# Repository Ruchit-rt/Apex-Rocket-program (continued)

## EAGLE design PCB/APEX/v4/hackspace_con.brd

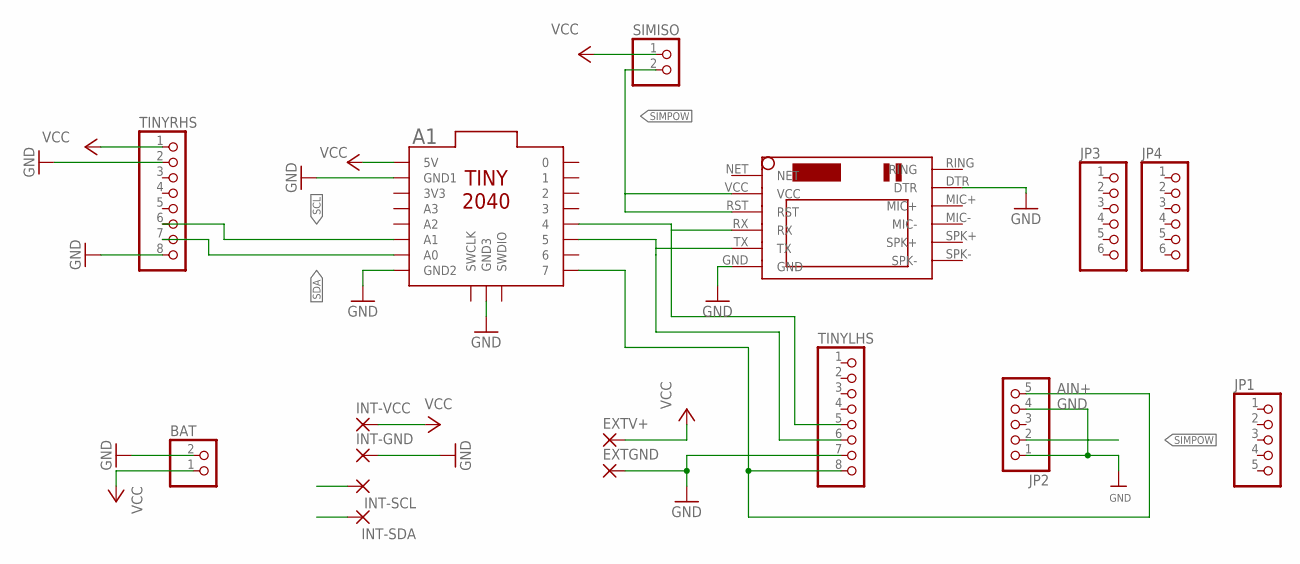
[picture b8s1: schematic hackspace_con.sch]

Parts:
A1: TINY2040
BAT: JST_2PIN-THM-RA; JST-PH-2-THM-RA
EXTGND: SMD5; SMD2,54-5,08
EXTV+: SMD5; SMD2,54-5,08
INT-GND: 3,17/1,1
INT-SCL: 3,17/1,1
INT-SDA: 3,17/1,1
INT-VCC: 3,17/1,1
JP1: PINHD-1X5; 1X05
JP2: HEADER-1X570MIL; 1X05_ROUND_70
JP3, JP4: PINHD-1X6; 1X06
SIMISO: PINHD-1X2; 1X02
TINYLHS: PINHD-1X8; 1X08
TINYRHS: PINHD-1X8; 1X08
U$1: SIM800LMODULE

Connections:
AIN+: A1.7, JP2.5, TINYLHS.8
GND: A1.GND1, A1.GND2, A1.GND3, BAT.2 (1), EXTGND.1, INT-GND.1, JP2.1, JP2.4, TINYLHS.7, TINYRHS.2, TINYRHS.8, U$1.DTR, U$1.GND
RX: A1.4, TINYLHS.5, U$1.RX
SCL: A1.A1, INT-SCL.1, TINYRHS.6
SDA: A1.A0, INT-SDA.1, TINYRHS.7
SIMPOW: JP2.2, SIMISO.2, U$1.RST, U$1.VCC
TX: A1.5, TINYLHS.6, U$1.TX
VCC: A1.5V, BAT.1 (2), EXTV+.1, INT-VCC.1, SIMISO.1, TINYRHS.1

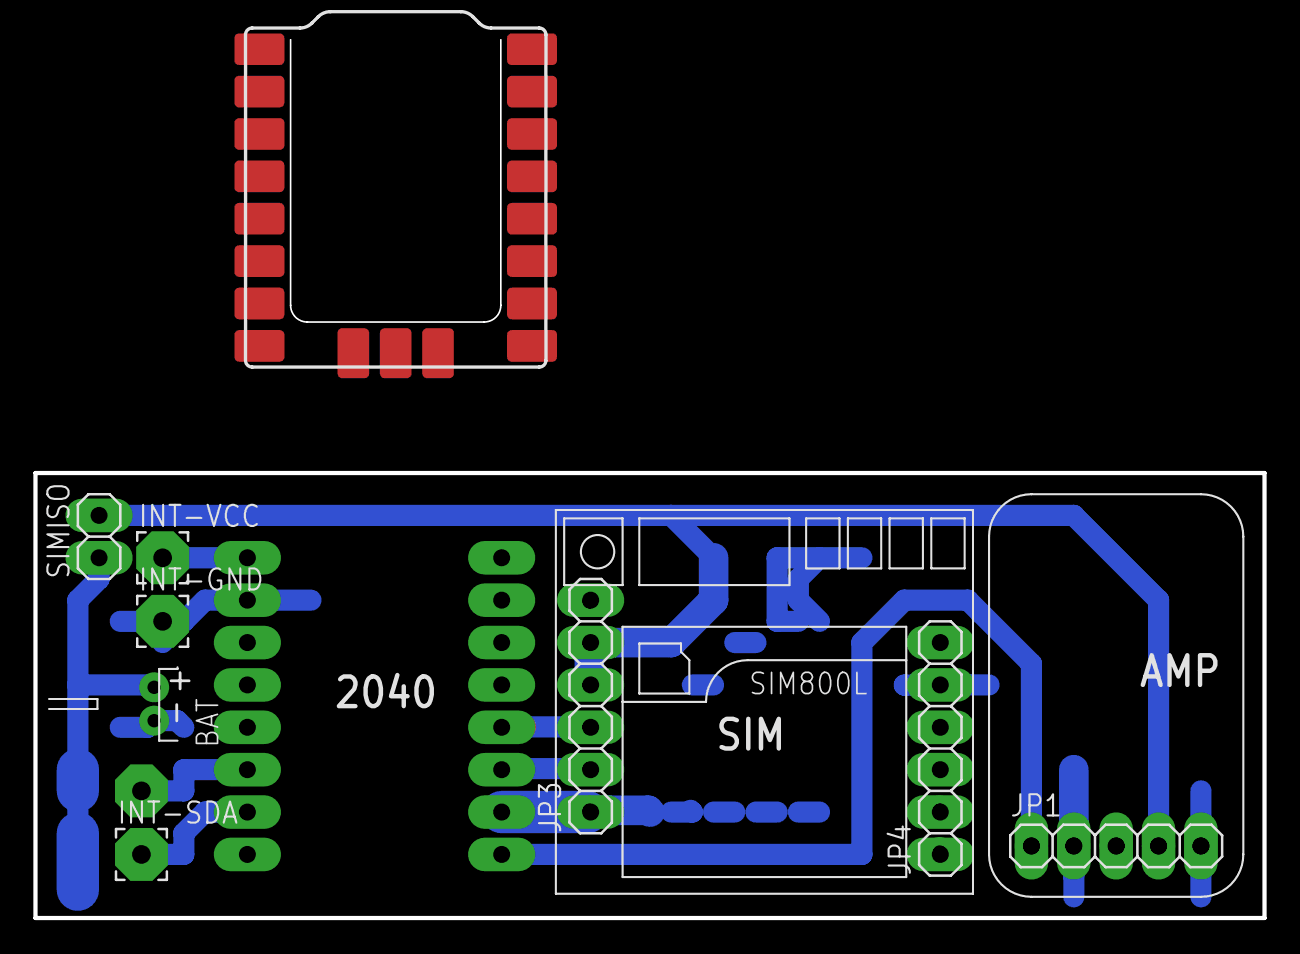
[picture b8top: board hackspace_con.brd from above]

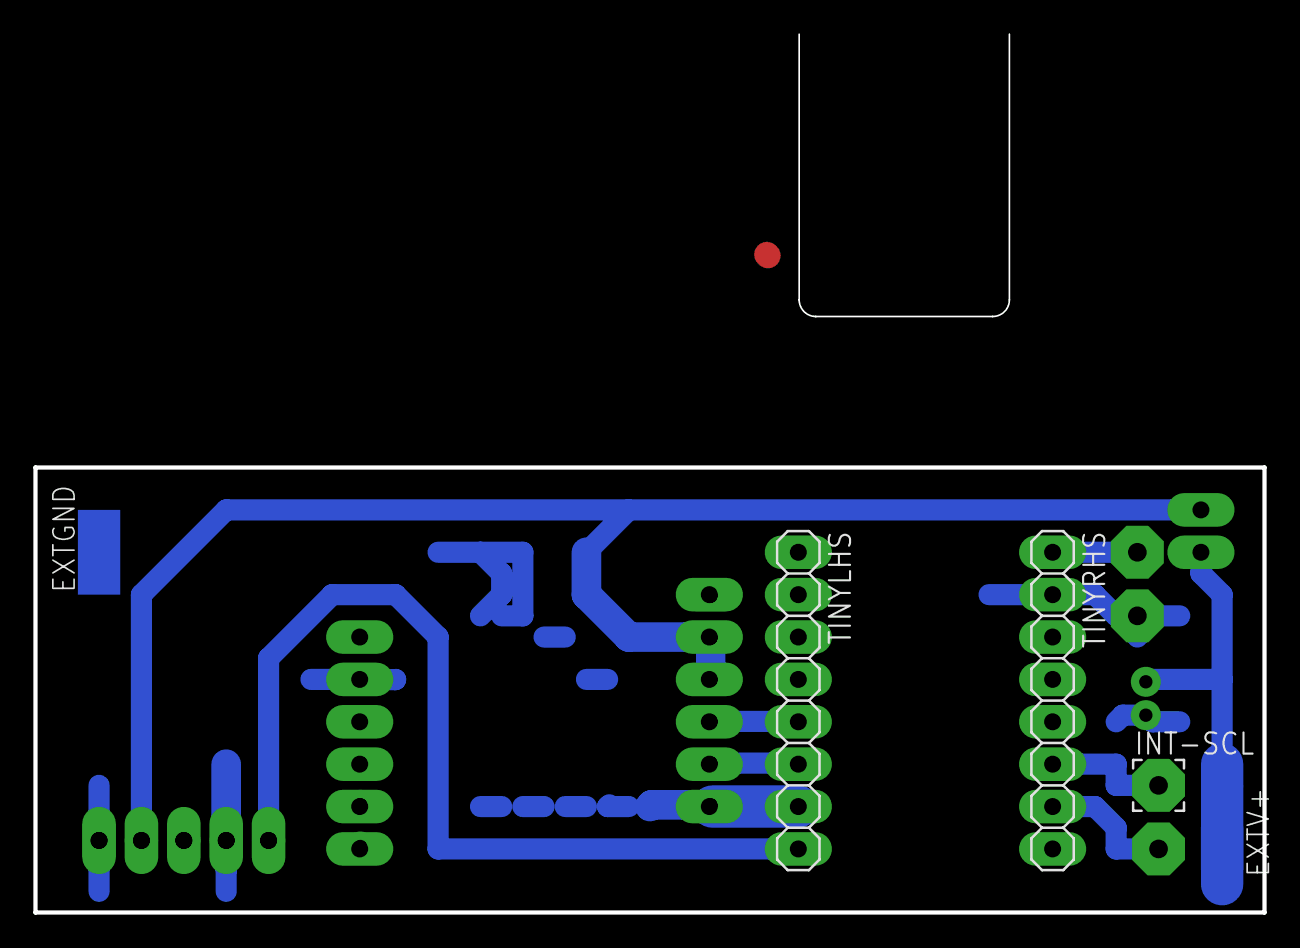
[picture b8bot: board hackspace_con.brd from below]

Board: 2 copper layers, 73.7 x 26.7 mm, 16 parts (5 on the bottom side), 8 nets.

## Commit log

2022-06-19 src and pcb code
2022-06-19 incorrect README
